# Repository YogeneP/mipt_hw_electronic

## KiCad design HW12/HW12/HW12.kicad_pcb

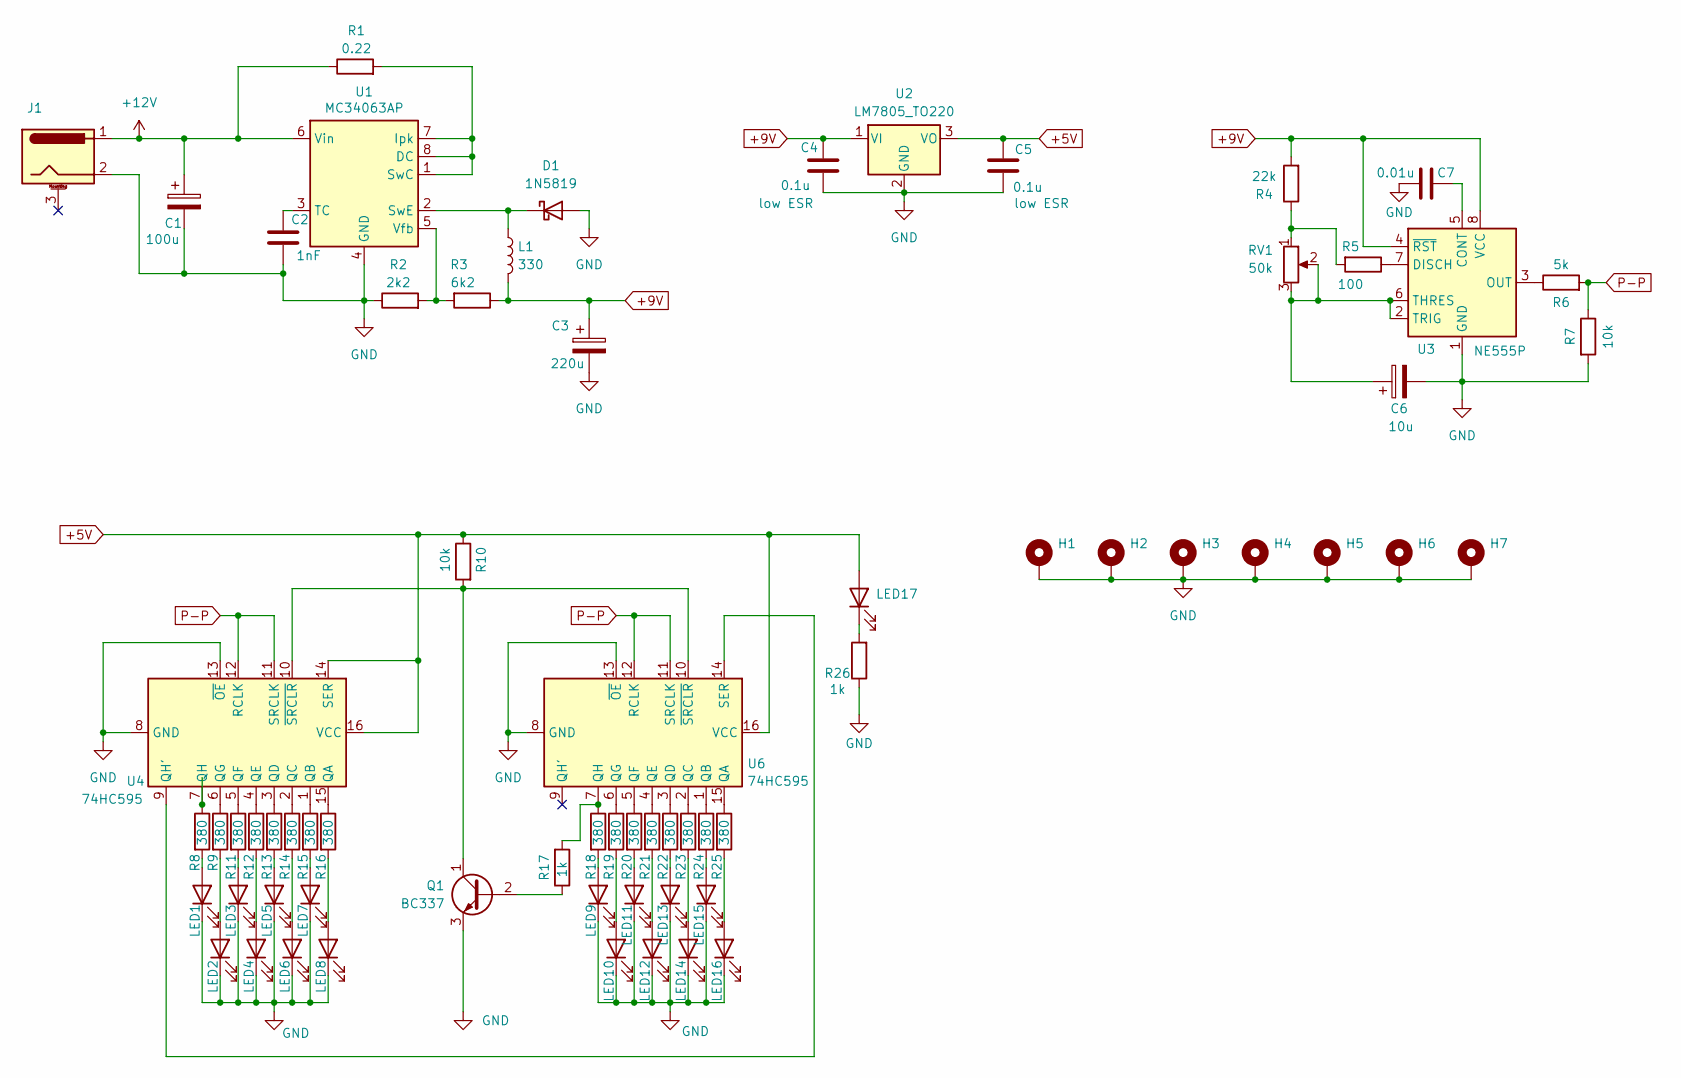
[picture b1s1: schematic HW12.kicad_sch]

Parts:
C1: 100u; CP_Radial_D4.0mm_P1.50mm
C2: 1nF; C_1206_3216Metric_Pad1.33x1.80mm_HandSolder
C3: 220u; CP_Radial_D4.0mm_P1.50mm
C4, C5: 0.1u; C_1206_3216Metric_Pad1.33x1.80mm_HandSolder
C6: 10u; CP_Radial_D4.0mm_P1.50mm
C7: 0.01u; C_1206_3216Metric_Pad1.33x1.80mm_HandSolder
D1: 1N5819; D_SMB_Handsoldering
H1, H2, H3, H4, H5, H6, H7: MountingHole_Pad; MountingHole_2.2mm_M2_DIN965_Pad
J1: Barrel_Jack_MountingPin; BarrelJack_Horizontal
L1: 330; L_Coilcraft_MSS1260-XXX
LED1, LED2, LED3, LED4, LED5, LED6, LED7, LED8, LED9, LED10, LED11, LED12, LED13, LED14, LED15, LED16, LED17: LED; LED_1206_3216Metric
Q1: BC337; TO-92_Inline
R1: 0.22; R_1206_3216Metric_Pad1.30x1.75mm_HandSolder
R2: 2k2; R_1206_3216Metric_Pad1.30x1.75mm_HandSolder
R3: 6k2; R_1206_3216Metric_Pad1.30x1.75mm_HandSolder
R4: 22k; R_1206_3216Metric_Pad1.30x1.75mm_HandSolder
R5: 100; R_1206_3216Metric_Pad1.30x1.75mm_HandSolder
R6: 5k; R_1206_3216Metric_Pad1.30x1.75mm_HandSolder
R7, R10: 10k; R_1206_3216Metric_Pad1.30x1.75mm_HandSolder
R8, R9, R11, R12, R13, R14, R15, R16, R18, R19, R20, R21, R22, R23, R24, R25: 380; R_1206_3216Metric_Pad1.30x1.75mm_HandSolder
R17, R26: 1k; R_1206_3216Metric_Pad1.30x1.75mm_HandSolder
RV1: 50k; Potentiometer_Alps_RK09K_Single_Vertical
U1: MC34063AP; DIP-8_W7.62mm
U2: LM7805_TO220; TO-252-2
U3: NE555P; DIP-8_W7.62mm
U4, U6: 74HC595; DIP-16_W7.62mm

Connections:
+5V: C5.1, LED17.2 (A), R10.1, U2.3 (VO), U4.14 (SER), U4.16 (VCC), U6.16 (VCC)
+9V: C3.1, C4.1, L1.2, R3.1, R4.2, U2.1 (VI), U3.4 (~RST), U3.8 (VCC)
+12V: C1.1, J1.1, R1.1, U1.6 (Vin)
GND: C1.2, C2.2, C3.2, C4.2, C5.2, C6.2, C7.1, D1.2 (A), H1.1, H2.1, H3.1, H4.1, H5.1, H6.1, H7.1, J1.2, LED1.1 (K), LED2.1 (K), LED3.1 (K), LED4.1 (K), LED5.1 (K), LED6.1 (K), LED7.1 (K), LED8.1 (K), LED9.1 (K), LED10.1 (K), LED11.1 (K), LED12.1 (K), LED13.1 (K), LED14.1 (K), LED15.1 (K), LED16.1 (K), Q1.3 (E), R2.1, R7.2, R26.1, U1.4 (GND), U2.2 (GND), U3.1 (GND), U4.8 (GND), U4.13 (~OE), U6.8 (GND), U6.13 (~OE)
unnamed: D1.1 (K), L1.1, U1.2 (SwE)
unnamed: LED1.2 (A), R8.2
unnamed: LED2.2 (A), R9.2
unnamed: LED3.2 (A), R11.2
unnamed: LED4.2 (A), R12.2
unnamed: LED5.2 (A), R13.2
unnamed: LED6.2 (A), R14.2
unnamed: LED7.2 (A), R15.2
unnamed: LED8.2 (A), R16.2
unnamed: LED9.2 (A), R18.2
unnamed: LED10.2 (A), R19.2
unnamed: LED11.2 (A), R20.2
unnamed: LED12.2 (A), R21.2
unnamed: LED13.2 (A), R22.2
unnamed: LED14.2 (A), R23.2
unnamed: LED15.2 (A), R24.2
unnamed: LED16.2 (A), R25.2
unnamed: LED17.1 (K), R26.2
unnamed: Q1.2 (B), R17.1
unnamed: Q1.1 (C), R10.2, U4.10 (~SRCLR), U6.10 (~SRCLR)
unnamed: R4.1, R5.2, RV1.1
unnamed: R1.2, U1.1 (SwC), U1.7 (Ipk), U1.8 (DC)
unnamed: C2.1, U1.3 (TC)
unnamed: R2.2, R3.2, U1.5 (Vfb)
unnamed: C7.2, U3.5 (CONT)
unnamed: R5.1, U3.7 (DISCH)
unnamed: R6.1, U3.3 (OUT)
unnamed: C6.1, RV1.2, RV1.3, U3.2 (TRIG), U3.6 (THRES)
unnamed: R16.1, U4.15 (QA)
unnamed: R15.1, U4.1 (QB)
unnamed: R14.1, U4.2 (QC)
unnamed: R13.1, U4.3 (QD)
unnamed: R12.1, U4.4 (QE)
unnamed: R11.1, U4.5 (QF)
unnamed: R9.1, U4.6 (QG)
unnamed: U4.9 (QH'), U6.14 (SER)
unnamed: R8.1, U4.7 (QH)
unnamed: R25.1, U6.15 (QA)
unnamed: R24.1, U6.1 (QB)
unnamed: R23.1, U6.2 (QC)
unnamed: R22.1, U6.3 (QD)
unnamed: R21.1, U6.4 (QE)
unnamed: R20.1, U6.5 (QF)
unnamed: R19.1, U6.6 (QG)
unnamed: R17.2, R18.1, U6.7 (QH)
P-P: R6.2, R7.1, U4.11 (SRCLK), U4.12 (RCLK), U6.11 (SRCLK), U6.12 (RCLK)

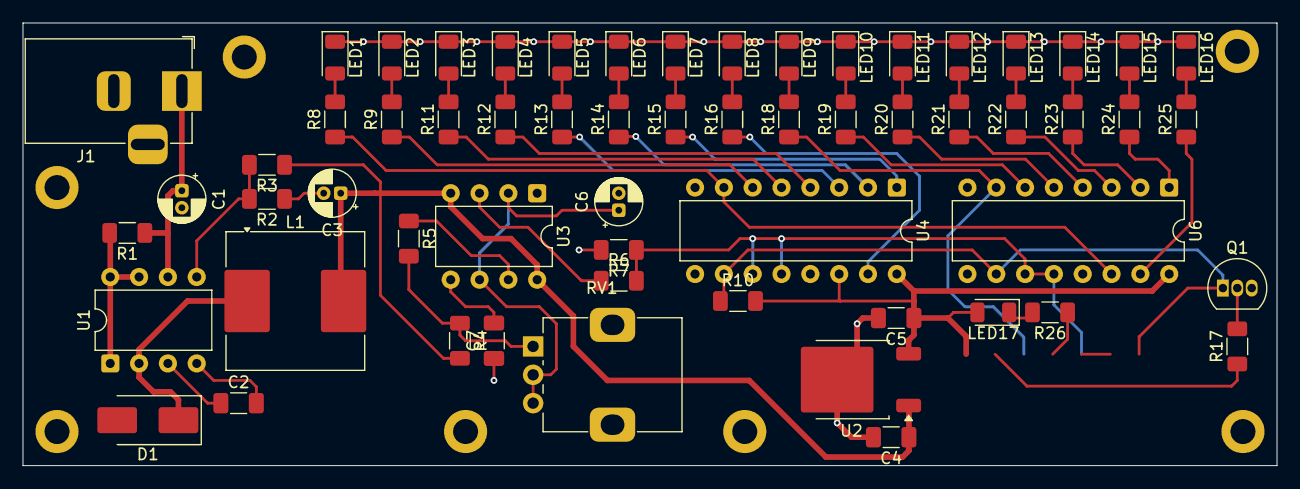
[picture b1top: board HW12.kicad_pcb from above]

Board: 2 copper layers, 110.5 x 39.0 mm, 67 parts (0 on the bottom side), 50 nets.

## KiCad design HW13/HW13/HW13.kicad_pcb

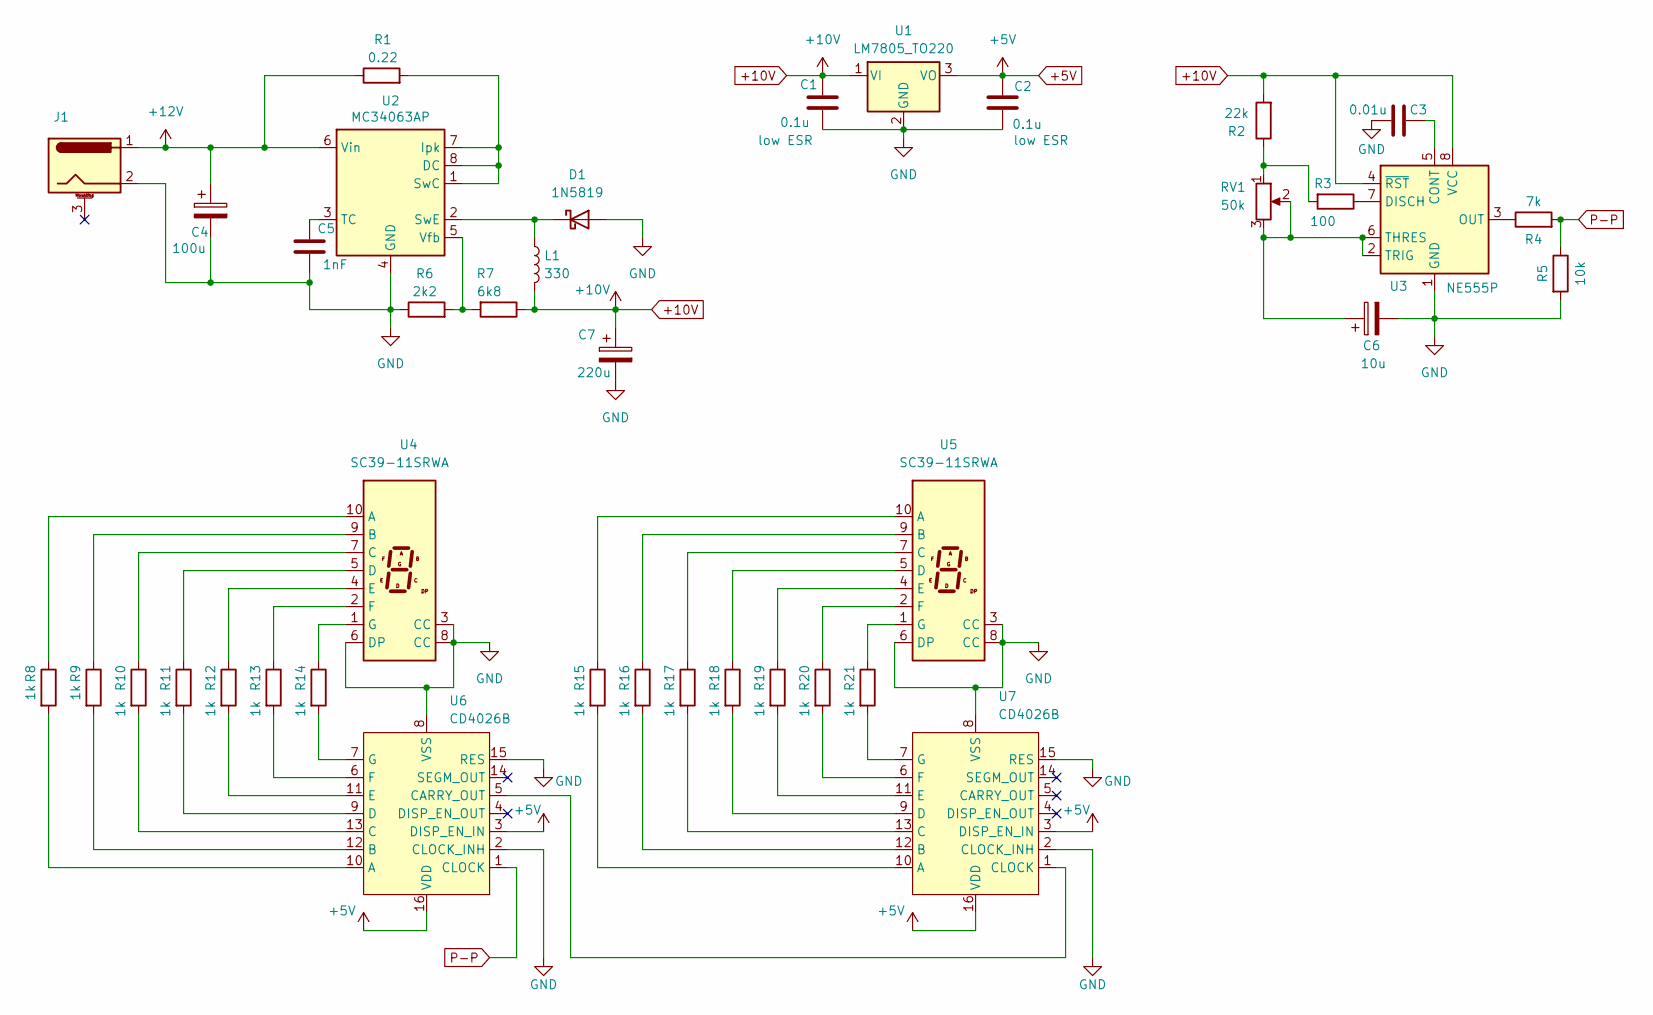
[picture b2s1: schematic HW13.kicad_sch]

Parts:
C1, C2: 0.1u; C_1206_3216Metric_Pad1.33x1.80mm_HandSolder
C3: 0.01u; C_1206_3216Metric_Pad1.33x1.80mm_HandSolder
C4: 100u; CP_Radial_D4.0mm_P1.50mm
C5: 1nF; C_1206_3216Metric_Pad1.33x1.80mm_HandSolder
C6: 10u; CP_Radial_D4.0mm_P1.50mm
C7: 220u; CP_Radial_D4.0mm_P1.50mm
D1: 1N5819; D_SMB_Handsoldering
J1: Barrel_Jack_MountingPin; BarrelJack_Horizontal
L1: 330; L_Coilcraft_MSS1260-XXX
R1: 0.22; R_1206_3216Metric_Pad1.30x1.75mm_HandSolder
R2: 22k; R_1206_3216Metric_Pad1.30x1.75mm_HandSolder
R3: 100; R_1206_3216Metric_Pad1.30x1.75mm_HandSolder
R4: 7k; R_1206_3216Metric_Pad1.30x1.75mm_HandSolder
R5: 10k; R_1206_3216Metric_Pad1.30x1.75mm_HandSolder
R6: 2k2; R_1206_3216Metric_Pad1.30x1.75mm_HandSolder
R7: 6k8; R_1206_3216Metric_Pad1.30x1.75mm_HandSolder
R8, R9, R10, R11, R12, R13, R14, R15, R16, R17, R18, R19, R20, R21: 1k; R_1206_3216Metric_Pad1.30x1.75mm_HandSolder
RV1: 50k; Potentiometer_Alps_RK09K_Single_Vertical
U1: LM7805_TO220; TO-252-2
U2: MC34063AP; DIP-8_W7.62mm
U3: NE555P; DIP-8_W7.62mm
U4, U5: SC39-11SRWA; Sx39-1xxxxx
U6, U7: CD4026B; DIP-16_W7.62mm

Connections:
+5V: C2.1, U1.3 (VO), U6.3 (DISP_EN_IN), U6.16 (VDD), U7.3 (DISP_EN_IN), U7.16 (VDD)
+10V: C1.1, C7.1, L1.2, R2.2, R7.1, U1.1 (VI), U3.4 (~RST), U3.8 (VCC)
+12V: C4.1, J1.1, R1.1, U2.6 (Vin)
GND: C1.2, C2.2, C3.1, C4.2, C5.2, C6.2, C7.2, D1.2 (A), J1.2, R5.2, R6.1, U1.2 (GND), U2.4 (GND), U3.1 (GND), U4.3 (CC), U4.6 (DP), U4.8 (CC), U5.3 (CC), U5.6 (DP), U5.8 (CC), U6.2 (CLOCK_INH), U6.8 (VSS), U6.15 (RES), U7.2 (CLOCK_INH), U7.8 (VSS), U7.15 (RES)
unnamed: D1.1 (K), L1.1, U2.2 (SwE)
unnamed: R2.1, R3.2, RV1.1
unnamed: R1.2, U2.1 (SwC), U2.7 (Ipk), U2.8 (DC)
unnamed: C5.1, U2.3 (TC)
unnamed: R6.2, R7.2, U2.5 (Vfb)
unnamed: C3.2, U3.5 (CONT)
unnamed: R3.1, U3.7 (DISCH)
unnamed: R4.1, U3.3 (OUT)
unnamed: C6.1, RV1.2, RV1.3, U3.2 (TRIG), U3.6 (THRES)
unnamed: R8.1, U4.10 (A)
unnamed: R9.1, U4.9 (B)
unnamed: R10.1, U4.7 (C)
unnamed: R11.1, U4.5 (D)
unnamed: R12.1, U4.4 (E)
unnamed: R13.1, U4.2 (F)
unnamed: R14.1, U4.1 (G)
unnamed: R15.1, U5.10 (A)
unnamed: R16.1, U5.9 (B)
unnamed: R17.1, U5.7 (C)
unnamed: R18.1, U5.5 (D)
unnamed: R19.1, U5.4 (E)
unnamed: R20.1, U5.2 (F)
unnamed: R21.1, U5.1 (G)
unnamed: R8.2, U6.10 (A)
unnamed: R9.2, U6.12 (B)
unnamed: R10.2, U6.13 (C)
unnamed: U6.5 (CARRY_OUT), U7.1 (CLOCK)
unnamed: R11.2, U6.9 (D)
unnamed: R12.2, U6.11 (E)
unnamed: R13.2, U6.6 (F)
unnamed: R14.2, U6.7 (G)
unnamed: R15.2, U7.10 (A)
unnamed: R16.2, U7.12 (B)
unnamed: R17.2, U7.13 (C)
unnamed: R18.2, U7.9 (D)
unnamed: R19.2, U7.11 (E)
unnamed: R20.2, U7.6 (F)
unnamed: R21.2, U7.7 (G)
P-P: R4.2, R5.1, U6.1 (CLOCK)

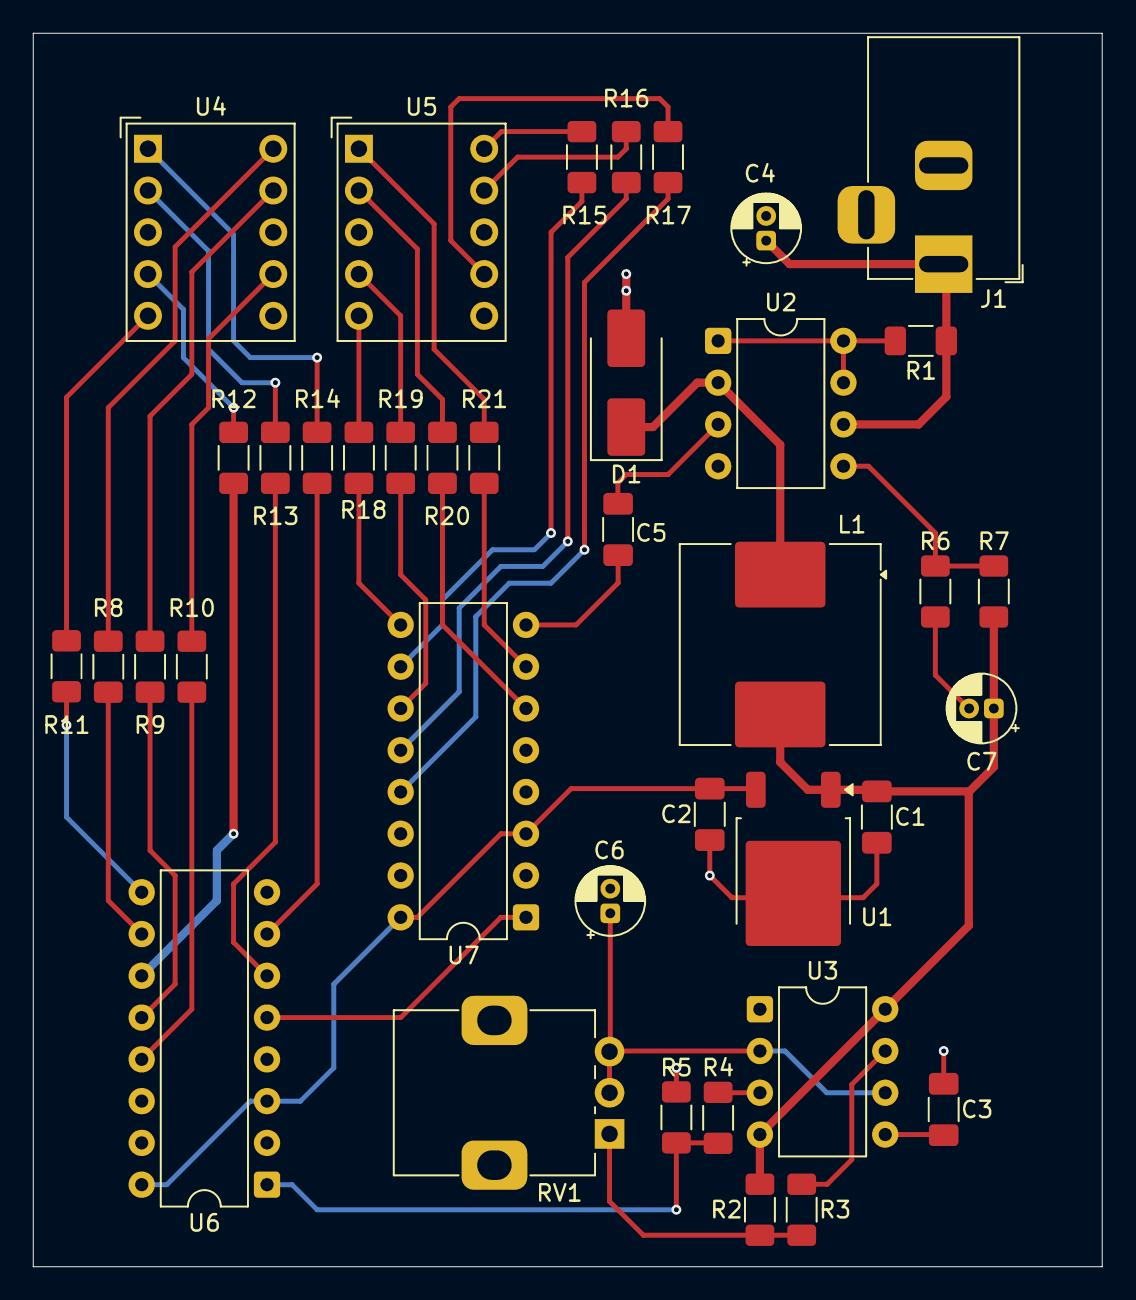
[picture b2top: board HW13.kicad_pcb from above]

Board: 2 copper layers, 65.0 x 75.0 mm, 39 parts (0 on the bottom side), 43 nets.

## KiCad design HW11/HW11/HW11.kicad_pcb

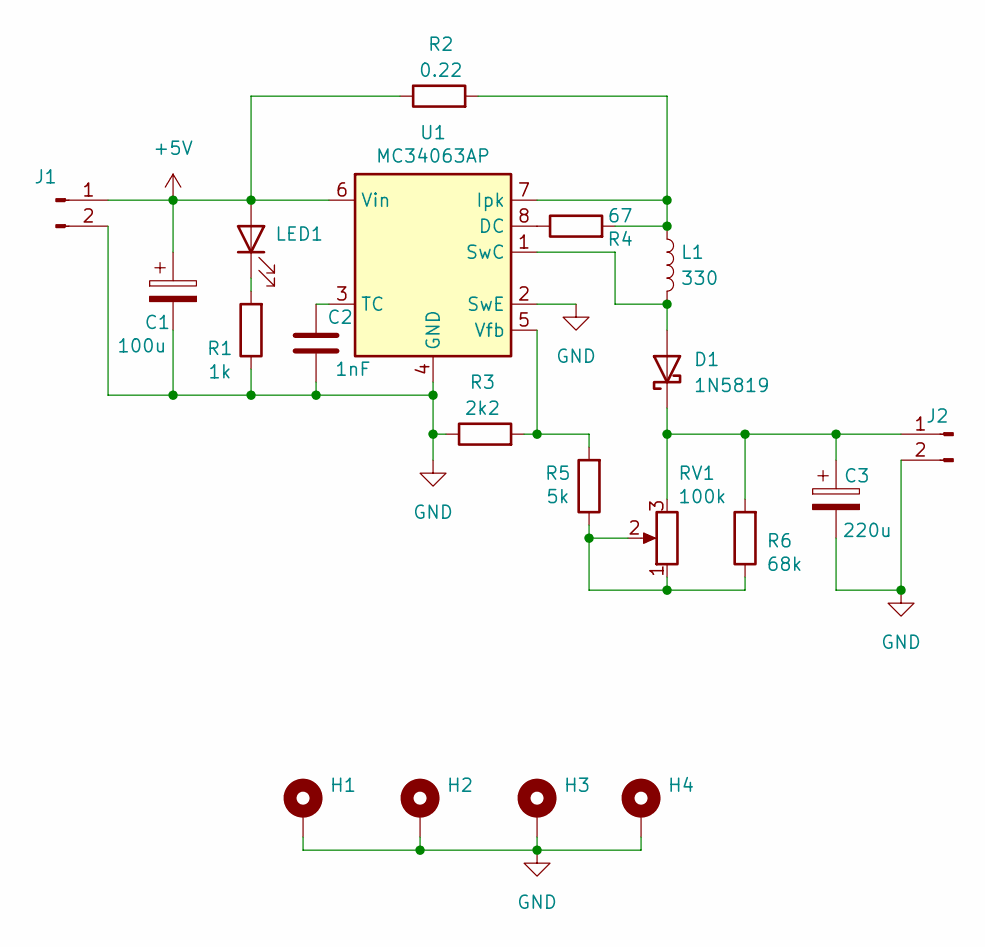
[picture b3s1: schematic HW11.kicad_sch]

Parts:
C1: 100u; CP_Radial_D4.0mm_P1.50mm
C2: 1nF; C_1206_3216Metric_Pad1.33x1.80mm_HandSolder
C3: 220u; CP_Radial_D4.0mm_P1.50mm
D1: 1N5819; D_SMB_Handsoldering
H1, H2, H3, H4: MountingHole_Pad; MountingHole_2.2mm_M2_Pad
J1, J2: Conn_01x02_Pin; PhoenixContact_GMSTBVA_2,5_2-G_1x02_P7.50mm_Vertical
L1: 330; L_Coilcraft_MSS1260-XXX
LED1: LED; LED_1206_3216Metric
R1: 1k; R_1206_3216Metric_Pad1.30x1.75mm_HandSolder
R2: 0.22; R_1206_3216Metric_Pad1.30x1.75mm_HandSolder
R3: 2k2; R_1206_3216Metric_Pad1.30x1.75mm_HandSolder
R4: 67; R_1206_3216Metric_Pad1.30x1.75mm_HandSolder
R5: 5k; R_1206_3216Metric_Pad1.30x1.75mm_HandSolder
R6: 68k; R_1206_3216Metric_Pad1.30x1.75mm_HandSolder
RV1: 100k; Potentiometer_Bourns_3296Y_Vertical
U1: MC34063AP; DIP-8_W7.62mm

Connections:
+5V: C1.1, J1.1, LED1.2 (A), R2.1, U1.6 (Vin)
GND: C1.2, C2.2, C3.2, H1.1, H2.1, H3.1, H4.1, J1.2, J2.2, R1.1, R3.1, U1.2 (SwE), U1.4 (GND)
unnamed: D1.2 (A), L1.2, U1.1 (SwC)
unnamed: C3.1, D1.1 (K), J2.1, R6.2, RV1.3
unnamed: LED1.1 (K), R1.2
unnamed: R5.1, R6.1, RV1.1, RV1.2
unnamed: R4.1, U1.8 (DC)
unnamed: L1.1, R2.2, R4.2, U1.7 (Ipk)
unnamed: C2.1, U1.3 (TC)
unnamed: R3.2, R5.2, U1.5 (Vfb)

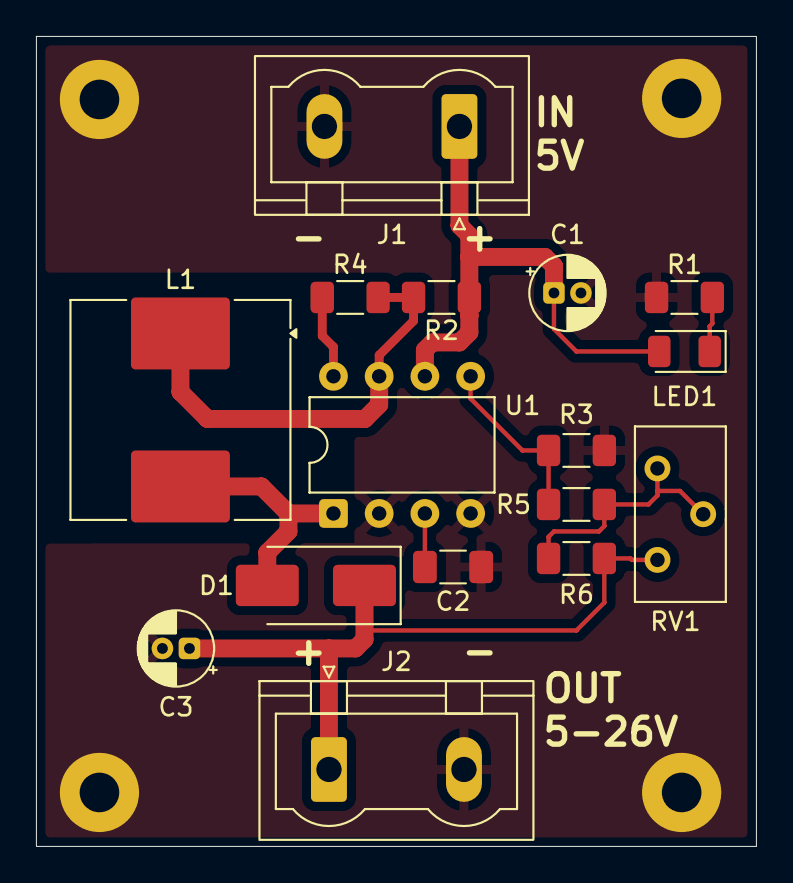
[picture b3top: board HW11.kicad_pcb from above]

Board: 2 copper layers, 40.0 x 45.0 mm, 20 parts (0 on the bottom side), 10 nets.

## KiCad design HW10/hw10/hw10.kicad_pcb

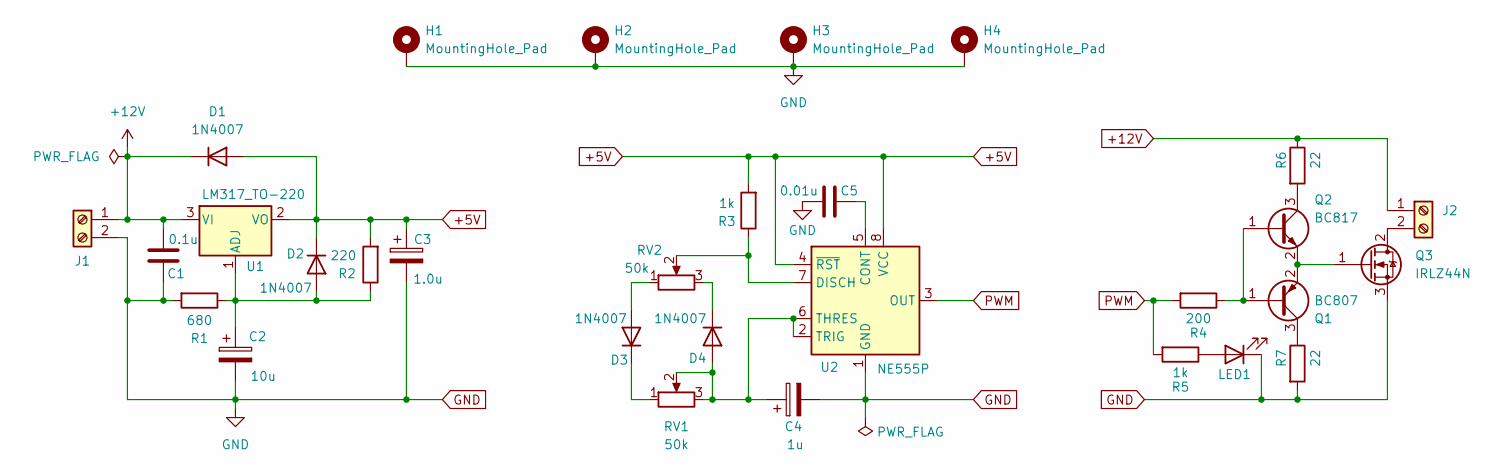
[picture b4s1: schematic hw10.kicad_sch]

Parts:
C1: 0.1u; C_1206_3216Metric_Pad1.33x1.80mm_HandSolder
C2: 10u; CP_Radial_D4.0mm_P1.50mm
C3: 1.0u; C_1206_3216Metric_Pad1.33x1.80mm_HandSolder
C4: 1u; CP_Radial_D4.0mm_P1.50mm
C5: 0.01u; C_1206_3216Metric_Pad1.33x1.80mm_HandSolder
D1, D2, D3, D4: 1N4007; D_SMA_Handsoldering
H1, H2, H3, H4: MountingHole_Pad; MountingHole_2.2mm_M2_DIN965_Pad
J1, J2: Screw_Terminal_01x02; TerminalBlock_Phoenix_MKDS-1,5-2-5.08_1x02_P5.08mm_Horizont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
LED1: LED; LED_1206_3216Metric_Pad1.42x1.75mm_HandSolder
Q1: BC807; SOT-23_Handsoldering
Q2: BC817; SOT-23_Handsoldering
Q3: IRLZ44N; TO-220-3_Vertical
R1: 680; R_1206_3216Metric_Pad1.30x1.75mm_HandSolder
R2: 220; R_1206_3216Metric_Pad1.30x1.75mm_HandSolder
R3, R5: 1k; R_1206_3216Metric_Pad1.30x1.75mm_HandSolder
R4: 200; R_1206_3216Metric_Pad1.30x1.75mm_HandSolder
R6, R7: 22; R_1206_3216Metric_Pad1.30x1.75mm_HandSolder
RV1, RV2: 50k; Potentiometer_Alps_RK09K_Single_Vertical
U1: LM317_TO-220; TO-220-3_Vertical
U2: NE555P; DIP-8_W7.62mm

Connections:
+5V: C3.1, D1.2 (A), D2.1 (K), R2.2, R3.2, U1.2 (VO), U2.4 (~RST), U2.8 (VCC)
+12V: C1.2, D1.1 (K), J1.1, J2.1, R6.1, U1.3 (VI)
GND: C1.1, C2.2, C3.2, C4.2, C5.1, H1.1, H2.1, H3.1, H4.1, J1.2, LED1.1 (K), Q3.3 (S), R1.2, R7.2, U2.1 (GND)
unnamed: C2.1, D2.2 (A), R1.1, R2.1, U1.1 (ADJ)
unnamed: D3.2 (A), RV2.1
unnamed: D3.1 (K), RV1.1
unnamed: C4.1, D4.2 (A), RV1.2, RV1.3, U2.2 (TRIG), U2.6 (THRES)
unnamed: D4.1 (K), RV2.3
unnamed: J2.2, Q3.2 (D)
unnamed: LED1.2 (A), R5.1
unnamed: Q1.1 (B), Q2.1 (B), R4.1
unnamed: Q1.3 (C), R7.1
unnamed: Q1.2 (E), Q2.2 (E), Q3.1 (G)
unnamed: Q2.3 (C), R6.2
unnamed: C5.2, U2.5 (CONT)
unnamed: R3.1, RV2.2, U2.7 (DISCH)
PWM: R4.2, R5.2, U2.3 (OUT)

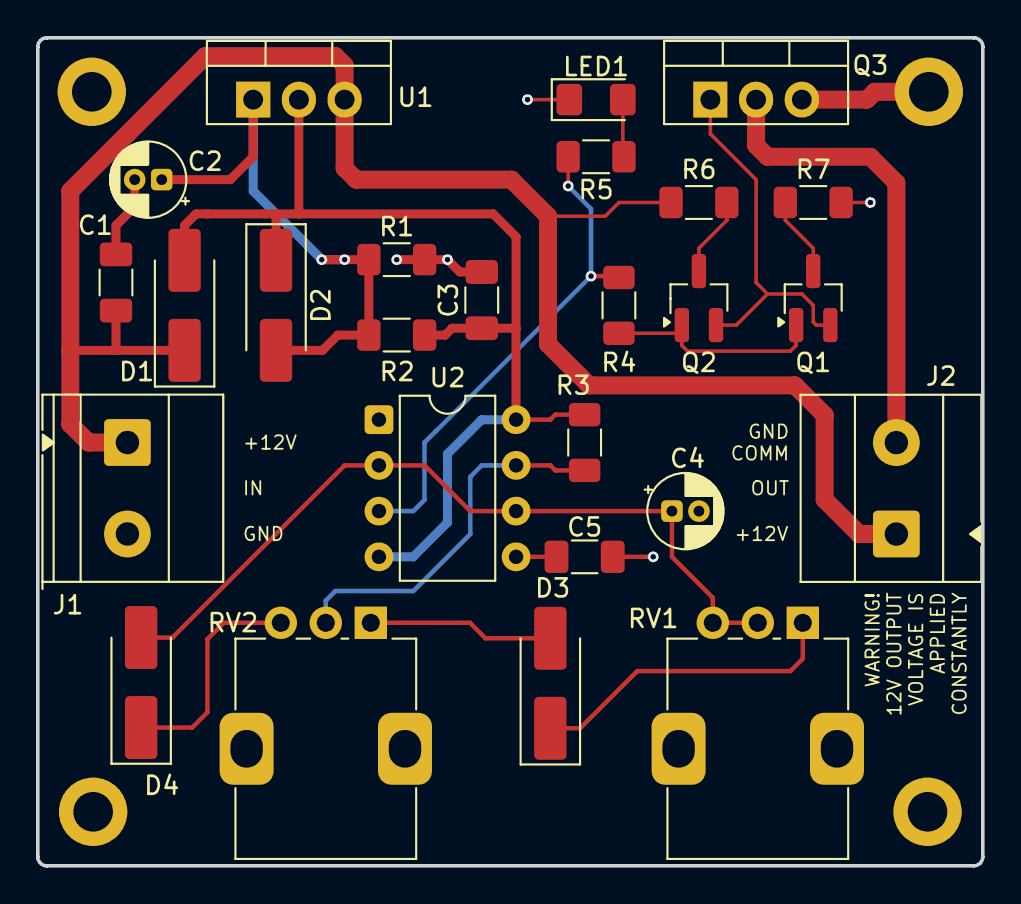
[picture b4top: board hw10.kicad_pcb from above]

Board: 2 copper layers, 52.5 x 46.0 mm, 30 parts (0 on the bottom side), 17 nets.

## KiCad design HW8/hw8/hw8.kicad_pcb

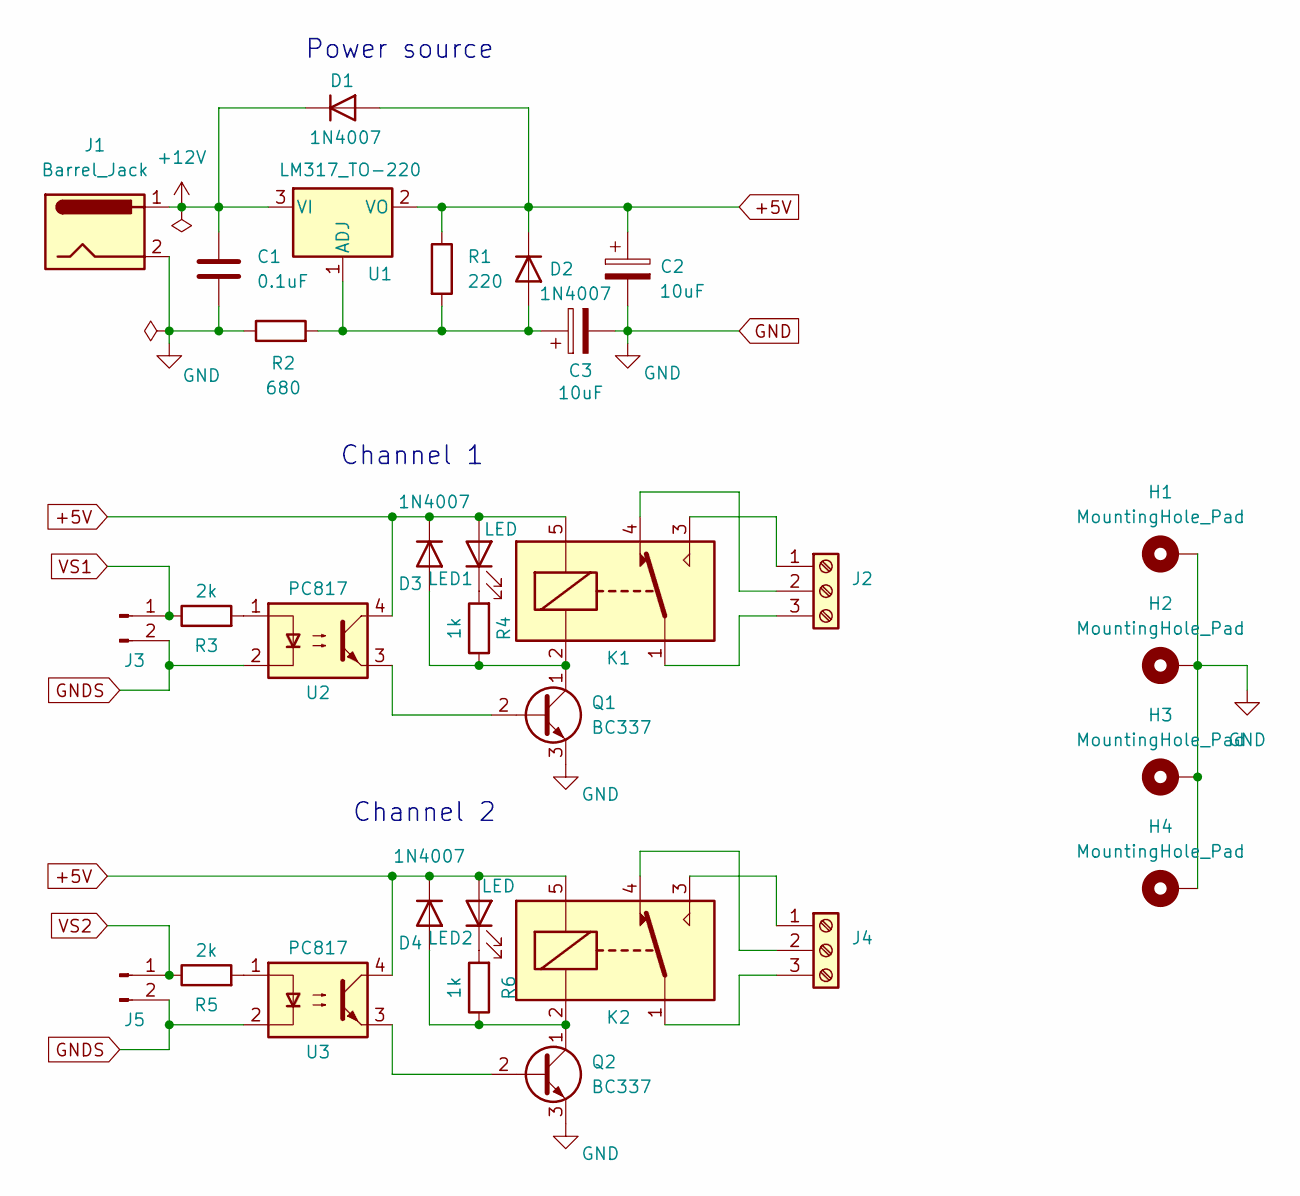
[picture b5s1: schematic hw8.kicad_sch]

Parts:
C1: 0.1uF; C_1206_3216Metric_Pad1.33x1.80mm_HandSolder
C2, C3: 10uF; CP_Radial_D4.0mm_P1.50mm
D1, D2, D3, D4: 1N4007; D_1206_3216Metric
H1, H2, H3, H4: MountingHole_Pad; MountingHole_2.2mm_M2_DIN965_Pad
J1: Barrel_Jack; BarrelJack_GCT_DCJ200-10-A_Horizontal
J2: Comm 1 Terminal; TerminalBlock_Phoenix_MKDS-1,5-3-5.08_1x03_P5.08mm_Horizont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
J3, J5: Conn_01x02_Pin; Molex_KK-254_AE-6410-02A_1x02_P2.54mm_Vertical
J4: Comm 2 Terminal; TerminalBlock_Phoenix_MKDS-1,5-3-5.08_1x03_P5.08mm_Horizont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
K1, K2: SANYOU_SRD_Form_C; Relay_SPDT_SANYOU_SRD_Series_Form_C
LED1, LED2: LED; LED_1206_3216Metric
Q1, Q2: BC337; TO-92_Inline
R1: 220; R_1206_3216Metric_Pad1.30x1.75mm_HandSolder
R2: 680; R_1206_3216Metric_Pad1.30x1.75mm_HandSolder
R3, R5: 2k; R_1206_3216Metric_Pad1.30x1.75mm_HandSolder
R4, R6: 1k; R_1206_3216Metric_Pad1.30x1.75mm_HandSolder
U1: LM317_TO-220; TO-220-3_Vertical
U2, U3: PC817; DIP-4_W7.62mm

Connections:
+5V: C2.1, D1.2 (A), D2.1 (K), D3.1 (K), D4.1 (K), K1.5, K2.5, LED1.2 (A), LED2.2 (A), R1.1, U1.2 (VO), U2.4, U3.4
+12V: C1.1, D1.1 (K), J1.1, U1.3 (VI)
GND: C1.2, C2.2, C3.2, H1.1, H2.1, H3.1, H4.1, J1.2, Q1.3 (E), Q2.3 (E), R2.1
GNDS: J3.2, J5.2, U2.2, U3.2
unnamed: C3.1, D2.2 (A), R1.2, R2.2, U1.1 (ADJ)
unnamed: D3.2 (A), K1.2, Q1.1 (C), R4.1
unnamed: D4.2 (A), K2.2, Q2.1 (C), R6.1
unnamed: J2.1, K1.3
unnamed: J2.2, K1.4
unnamed: J2.3, K1.1
unnamed: J4.1, K2.3
unnamed: J4.2, K2.4
unnamed: J4.3, K2.1
unnamed: LED1.1 (K), R4.2
unnamed: LED2.1 (K), R6.2
unnamed: Q1.2 (B), U2.3
unnamed: Q2.2 (B), U3.3
unnamed: R3.2, U2.1
unnamed: R5.2, U3.1
VS1: J3.1, R3.1
VS2: J5.1, R5.1

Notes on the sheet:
Channel 1
Channel 2
Power source

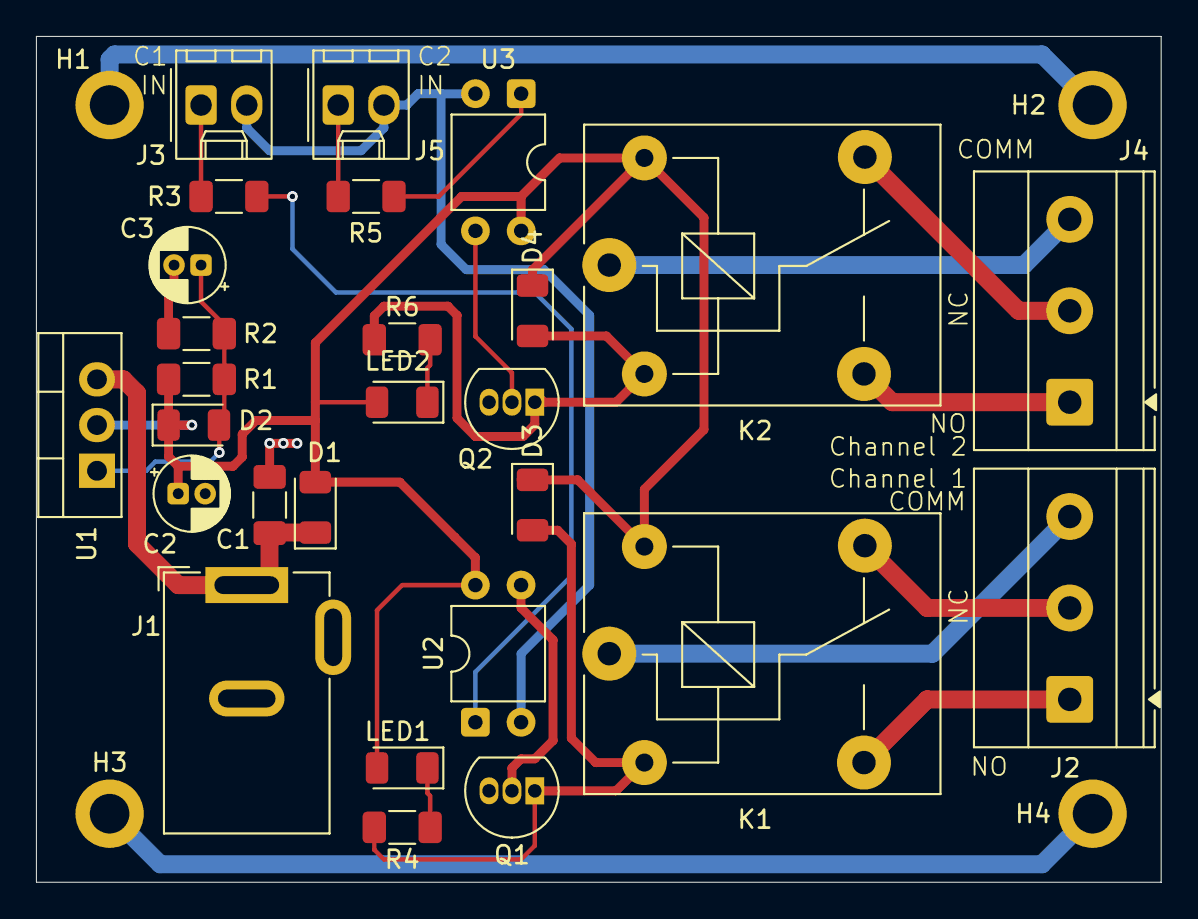
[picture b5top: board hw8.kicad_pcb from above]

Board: 2 copper layers, 62.5 x 47.0 mm, 31 parts (0 on the bottom side), 21 nets.

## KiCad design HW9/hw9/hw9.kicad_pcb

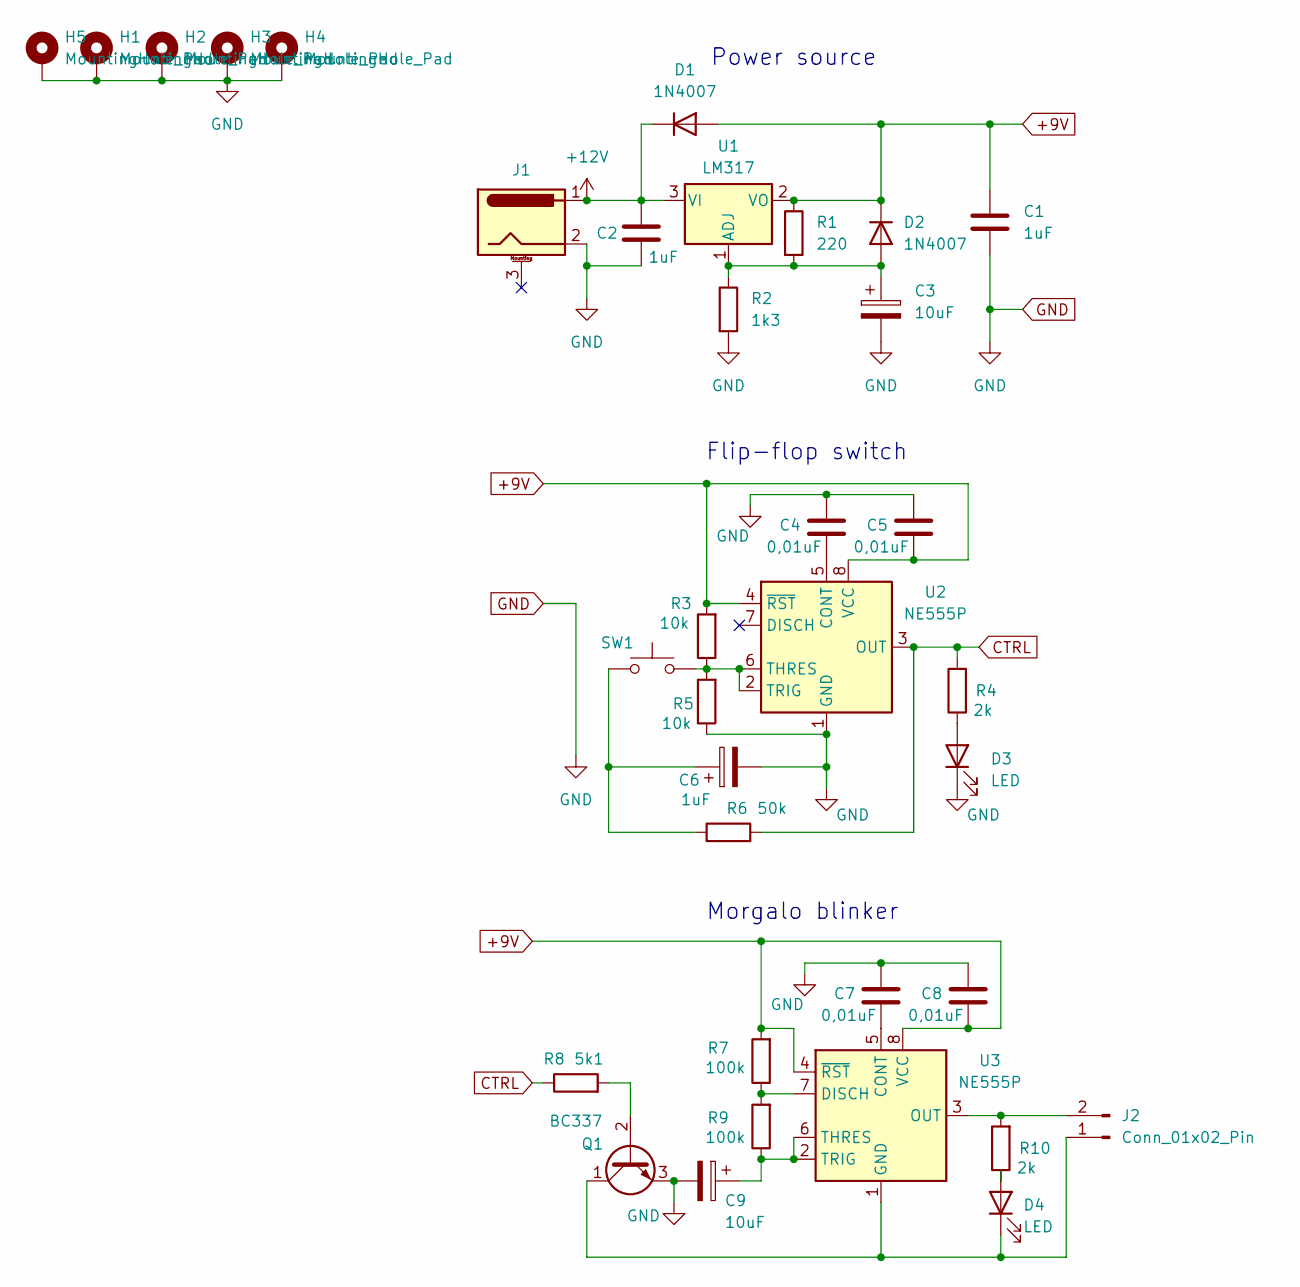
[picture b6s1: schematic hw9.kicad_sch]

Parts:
C1, C2: 1uF; CP_Radial_Tantal_D4.5mm_P2.50mm
C3, C9: 10uF; CP_Radial_D4.0mm_P1.50mm
C4, C5, C7, C8: 0,01uF; C_1206_3216Metric_Pad1.33x1.80mm_HandSolder
C6: 1uF; CP_Radial_D4.0mm_P1.50mm
D1, D2: 1N4007; D_SOD-123
D3, D4: LED; LED_2010_5025Metric
H1, H2, H3, H4, H5: MountingHole_Pad; MountingHole_2.2mm_M2_DIN965_Pad
J1: Barrel_Jack_MountingPin; BarrelJack_Horizontal
J2: Conn_01x02_Pin; Molex_PicoBlade_53261-0271_1x02-1MP_P1.25mm_Horizontal
Q1: BC337; TO-92_Inline
R1: 220; R_1206_3216Metric_Pad1.30x1.75mm_HandSolder
R2: 1k3; R_1206_3216Metric_Pad1.30x1.75mm_HandSolder
R3, R5: 10k; R_1206_3216Metric_Pad1.30x1.75mm_HandSolder
R4, R10: 2k; R_1206_3216Metric_Pad1.30x1.75mm_HandSolder
R6: 50k; R_1206_3216Metric_Pad1.30x1.75mm_HandSolder
R7, R9: 100k; R_1206_3216Metric_Pad1.30x1.75mm_HandSolder
R8: 5k1; R_1206_3216Metric_Pad1.30x1.75mm_HandSolder
SW1: SW_MEC_5G; SW_PUSH-12mm
U1: LM317; TO-220-3_Vertical
U2, U3: NE555P; DIP-8_W7.62mm

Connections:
+9V: C1.1, C5.2, C8.2, D1.2 (A), D2.1 (K), R1.1, R3.2, R7.2, U1.2 (VO), U2.4 (~RST), U2.8 (VCC), U3.4 (~RST), U3.8 (VCC)
+12V: C2.1, D1.1 (K), J1.1, U1.3 (VI)
CTRL: R4.2, R6.2, R8.1, U2.3 (OUT)
GND: C1.2, C2.2, C3.2, C4.1, C5.1, C6.2, C7.1, C8.1, C9.2, D3.1 (K), H1.1, H2.1, H3.1, H4.1, H5.1, J1.2, Q1.3 (E), R2.2, R5.1, U2.1 (GND)
unnamed: C3.1, D2.2 (A), R1.2, R2.1, U1.1 (ADJ)
unnamed: D3.2 (A), R4.1
unnamed: D4.2 (A), R10.1
unnamed: D4.1 (K), J2.1, Q1.1 (C), U3.1 (GND)
unnamed: J2.2, R10.2, U3.3 (OUT)
unnamed: Q1.2 (B), R8.2
unnamed: C6.1, R6.1, SW1.1 (A)
unnamed: R3.1, R5.2, SW1.2 (B), U2.2 (TRIG), U2.6 (THRES)
unnamed: C4.2, U2.5 (CONT)
unnamed: C7.2, U3.5 (CONT)
unnamed: R7.1, R9.2, U3.7 (DISCH)
unnamed: C9.1, R9.1, U3.2 (TRIG), U3.6 (THRES)

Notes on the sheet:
Flip-flop switch
Morgalo blinker
Power source

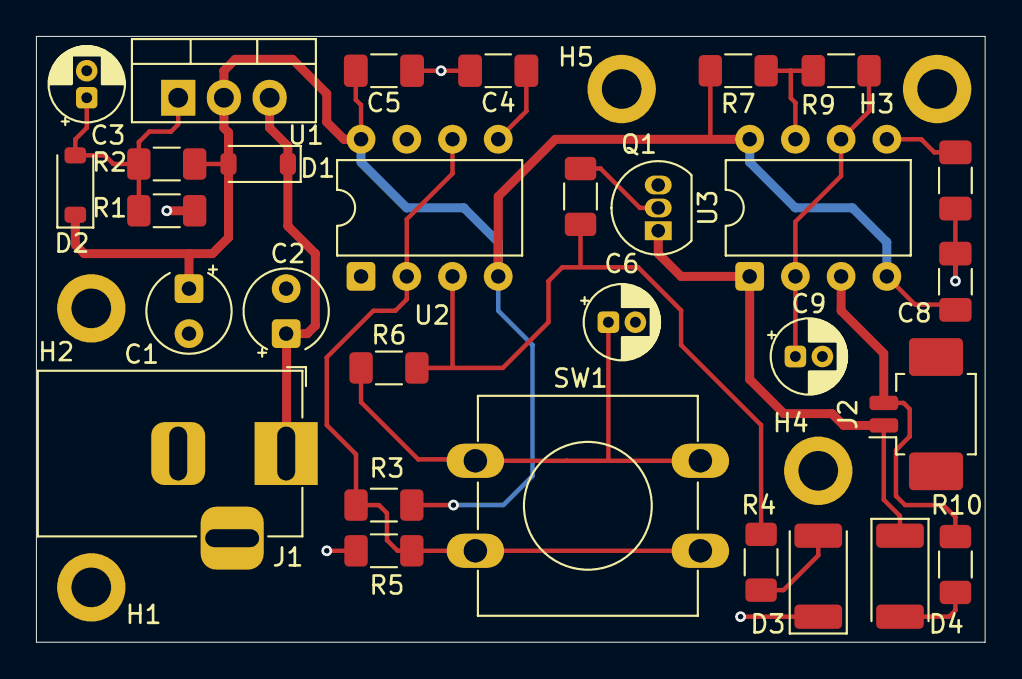
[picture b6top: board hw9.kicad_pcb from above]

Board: 2 copper layers, 52.7 x 33.7 mm, 35 parts (0 on the bottom side), 16 nets.
